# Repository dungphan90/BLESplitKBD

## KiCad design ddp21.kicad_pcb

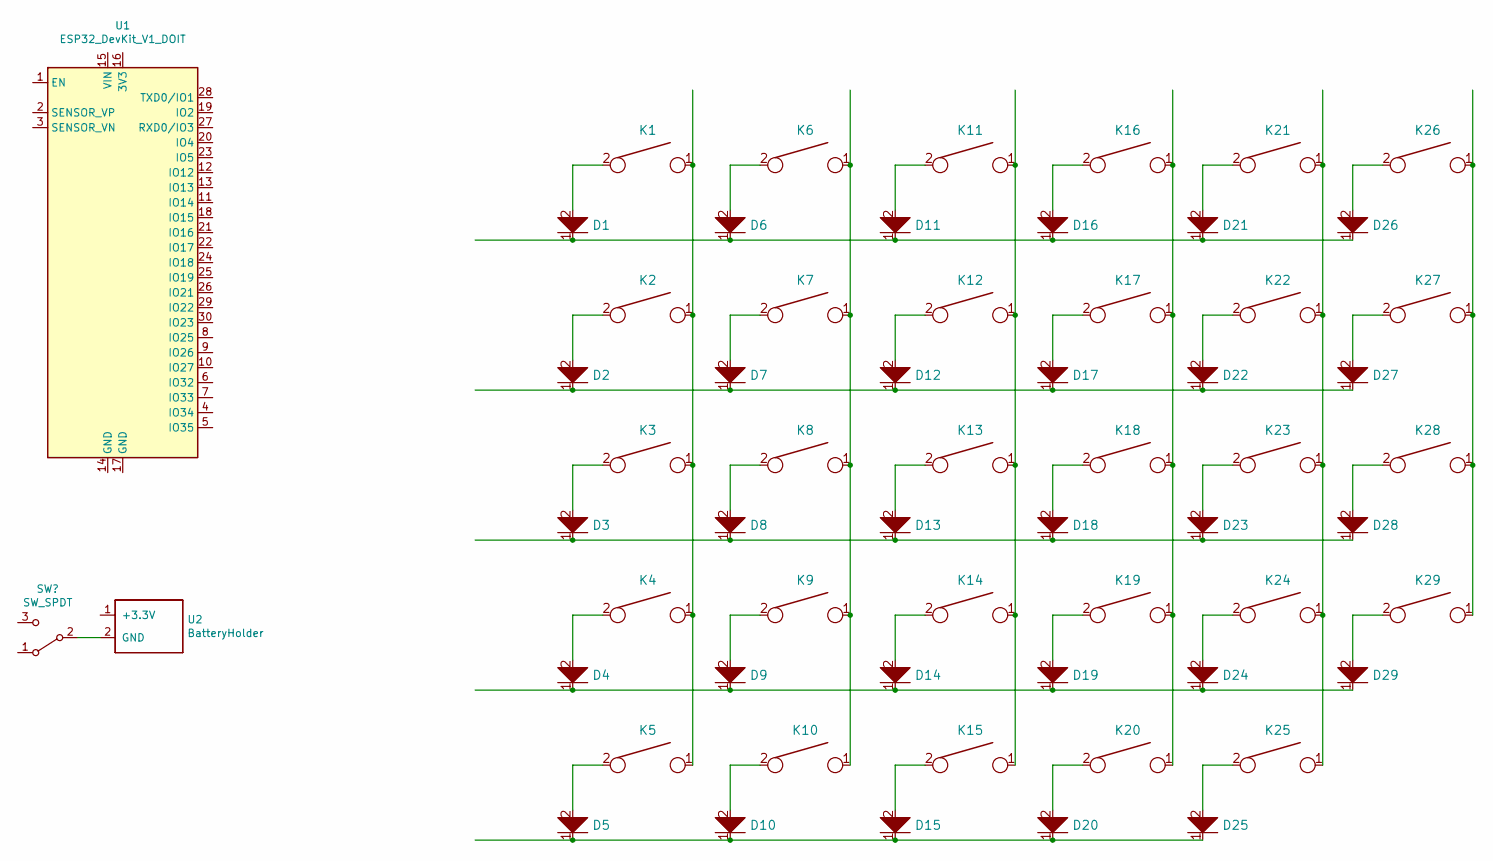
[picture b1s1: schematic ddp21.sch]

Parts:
D1, D2, D3, D4, D5, D6, D7, D8, D9, D10, D11, D12, D13, D14, D15, D16, D17, D18, D19, D20, D21, D22, D23, D24, D25, D26, D27, D28, D29: D; D_SOD123W_hand
K1, K2, K3, K4, K5, K6, K7, K8, K9, K10, K11, K12, K13, K14, K15, K16, K17, K18, K19, K20, K21, K22, K23, K24, K25, K26, K27, K28, K29: KEYSW; Kailh_socket_MX
U1: ESP32_DevKit_V1_DOIT; esp32_devkit_v1_doit
U2: BatteryHolder; Keystone_1058_1x2032-CoinCell

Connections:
unnamed: D1.1, D6.1, D11.1, D16.1, D21.1, D26.1
unnamed: D1.2, K1.2
unnamed: D2.2, K2.2
unnamed: D3.2, K3.2
unnamed: D4.2, K4.2
unnamed: D5.2, K5.2
unnamed: D6.2, K6.2
unnamed: D7.2, K7.2
unnamed: D8.2, K8.2
unnamed: D9.2, K9.2
unnamed: D5.1, D10.1, D15.1, D20.1, D25.1
unnamed: D10.2, K10.2
unnamed: D11.2, K11.2
unnamed: D2.1, D7.1, D12.1, D17.1, D22.1, D27.1
unnamed: D12.2, K12.2
unnamed: D3.1, D8.1, D13.1, D18.1, D23.1, D28.1
unnamed: D13.2, K13.2
unnamed: D4.1, D9.1, D14.1, D19.1, D24.1, D29.1
unnamed: D14.2, K14.2
unnamed: D15.2, K15.2
unnamed: D16.2, K16.2
unnamed: D17.2, K17.2
unnamed: D18.2, K18.2
unnamed: D19.2, K19.2
unnamed: D20.2, K20.2
unnamed: D21.2, K21.2
unnamed: D22.2, K22.2
unnamed: D23.2, K23.2
unnamed: D24.2, K24.2
unnamed: D25.2, K25.2
unnamed: D26.2, K26.2
unnamed: D27.2, K27.2
unnamed: D28.2, K28.2
unnamed: D29.2, K29.2
unnamed: K1.1, K2.1, K3.1, K4.1, K5.1
unnamed: K6.1, K7.1, K8.1, K9.1, K10.1
unnamed: K11.1, K12.1, K13.1, K14.1, K15.1
unnamed: K16.1, K17.1, K18.1, K19.1, K20.1
unnamed: K21.1, K22.1, K23.1, K24.1, K25.1
unnamed: K26.1, K27.1, K28.1, K29.1

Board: 2 copper layers, 60 parts (31 on the bottom side), 40 nets, no tracks yet.

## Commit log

2021-06-08 Sofle based bluetooth keyboard.
